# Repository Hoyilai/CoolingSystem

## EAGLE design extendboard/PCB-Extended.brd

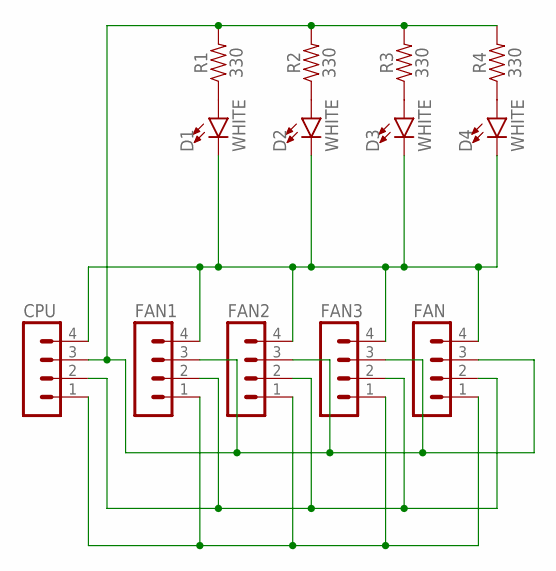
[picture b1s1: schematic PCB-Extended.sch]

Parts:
CPU: MA04-1
D1, D2, D3, D4: WHITE; LED-1206
FAN, FAN1, FAN2, FAN3: MA04-1
R1, R2, R3, R4: 330; 0603

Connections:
FAN: CPU.2, FAN.2, FAN1.2, FAN2.2, FAN3.2
unnamed: CPU.1, FAN.1, FAN1.1, FAN2.1, FAN3.1
unnamed: CPU.4, D1.C, D2.C, D3.C, D4.C, FAN.4, FAN1.4, FAN2.4, FAN3.4
unnamed: CPU.3, FAN.3, FAN1.3, FAN2.3, FAN3.3, R1.2, R2.2, R3.2, R4.2
unnamed: D1.A, R1.1
unnamed: D2.A, R2.1
unnamed: D3.A, R3.1
unnamed: D4.A, R4.1

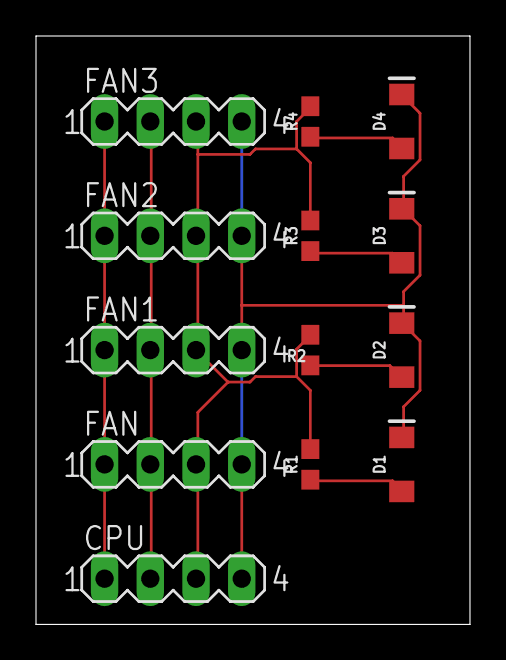
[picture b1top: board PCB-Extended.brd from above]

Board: 2 copper layers, 24.1 x 32.7 mm, 13 parts (0 on the bottom side), 8 nets.

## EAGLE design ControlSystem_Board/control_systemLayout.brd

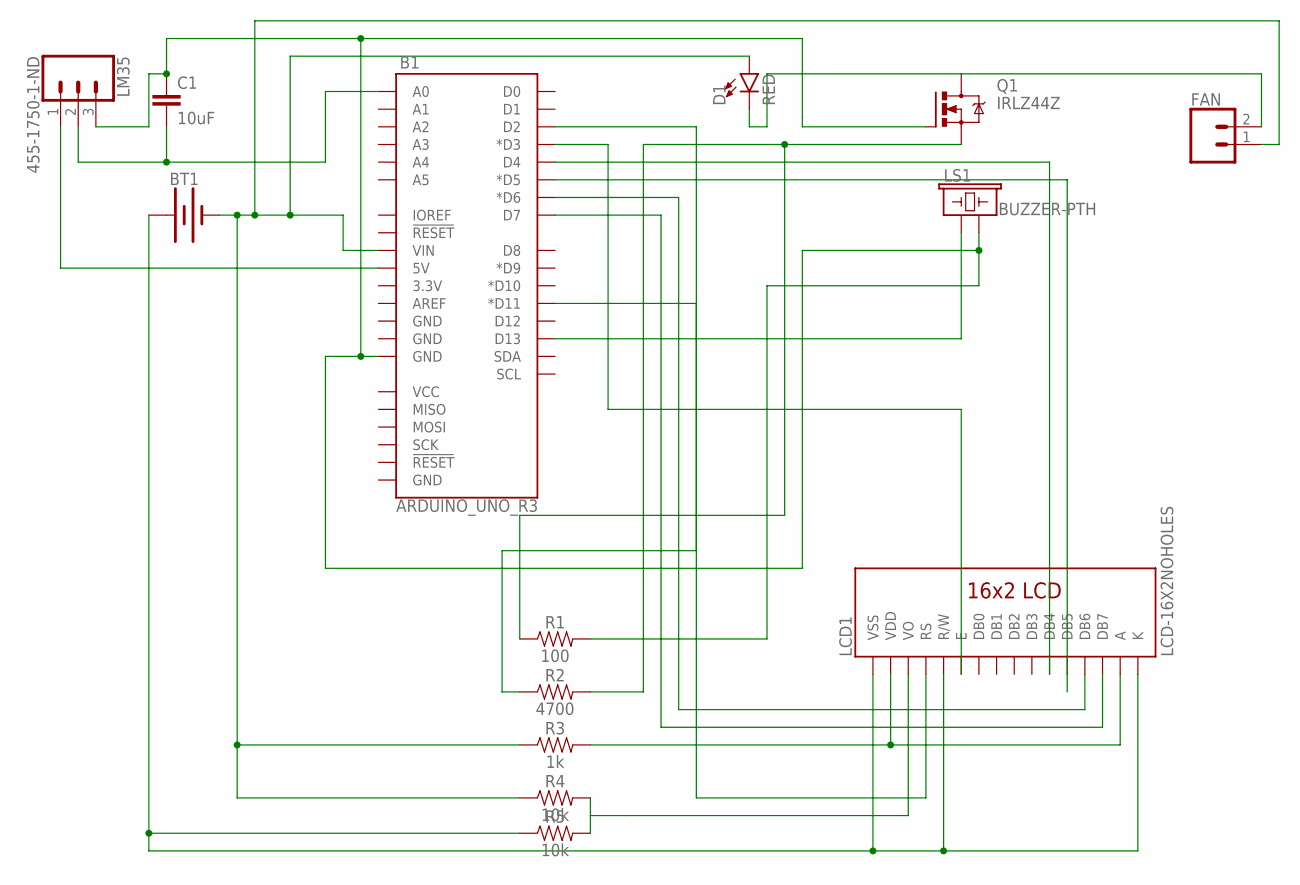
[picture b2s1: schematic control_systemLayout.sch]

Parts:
B1: ARDUINO_UNO_R3; ARDUINO_R3
BT1: BATTERY-9V; BATTCON_9V
C1: 10uF; 0603
D1: RED; LED-0603
FAN: CONN_02; 1X02
LCD1: LCD-16X2NOHOLES; LCD-16X2_NOHOLESNOSILK
LM35: 455-1750-1-ND; 1X03
LS1: BUZZER-PTH; BUZZER-12MM
Q1: IRLZ44Z; TO220BH
R1: 100; 0603
R2: 4700; 0603
R3: 1k; 0603
R4, R5: 10k; 0603

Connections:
unnamed: B1.VIN, BT1.-, D1.A, FAN.1, R3.1, R4.1
unnamed: B1.D13, LS1.+ (1)
unnamed: Q1.S, R1.1, R2.2
unnamed: D1.C, FAN.2, Q1.D
unnamed: B1.D11 (*D11), R2.1
unnamed: LCD1.2 (VDD), LCD1.15 (A), R3.2
unnamed: B1.GND@2 (GND), C1.1, LM35.3, LS1.- (2), Q1.G, R1.2
unnamed: B1.D7, LCD1.14 (DB7)
unnamed: BT1.+, LCD1.1 (VSS), LCD1.5 (R/W), LCD1.16 (K), R5.1
unnamed: B1.D6 (*D6), LCD1.13 (DB6)
unnamed: B1.D5 (*D5), LCD1.12 (DB5)
unnamed: B1.D4, LCD1.11 (DB4)
unnamed: B1.D3 (*D3), LCD1.6 (E)
unnamed: B1.D2, LCD1.4 (RS)
unnamed: LCD1.3 (VO), R4.2, R5.2
unnamed: B1.5V, LM35.1
unnamed: B1.A0, C1.2, LM35.2

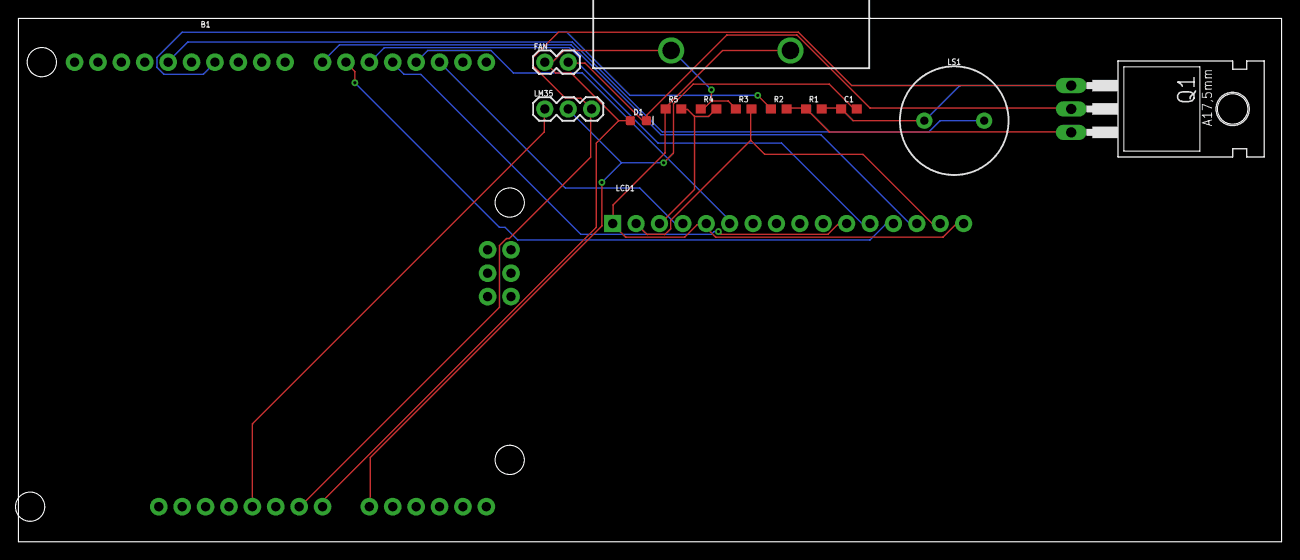
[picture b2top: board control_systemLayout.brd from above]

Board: 2 copper layers, 137.1 x 56.8 mm, 14 parts (0 on the bottom side), 17 nets.

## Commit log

2023-08-15 pcb_upload

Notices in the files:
parts and their libraries:
SparkFun-Boards: Licensing: Creative Commons ShareAlike 4.0 International - https://creativecommons.org/licenses/by-sa/4.0
